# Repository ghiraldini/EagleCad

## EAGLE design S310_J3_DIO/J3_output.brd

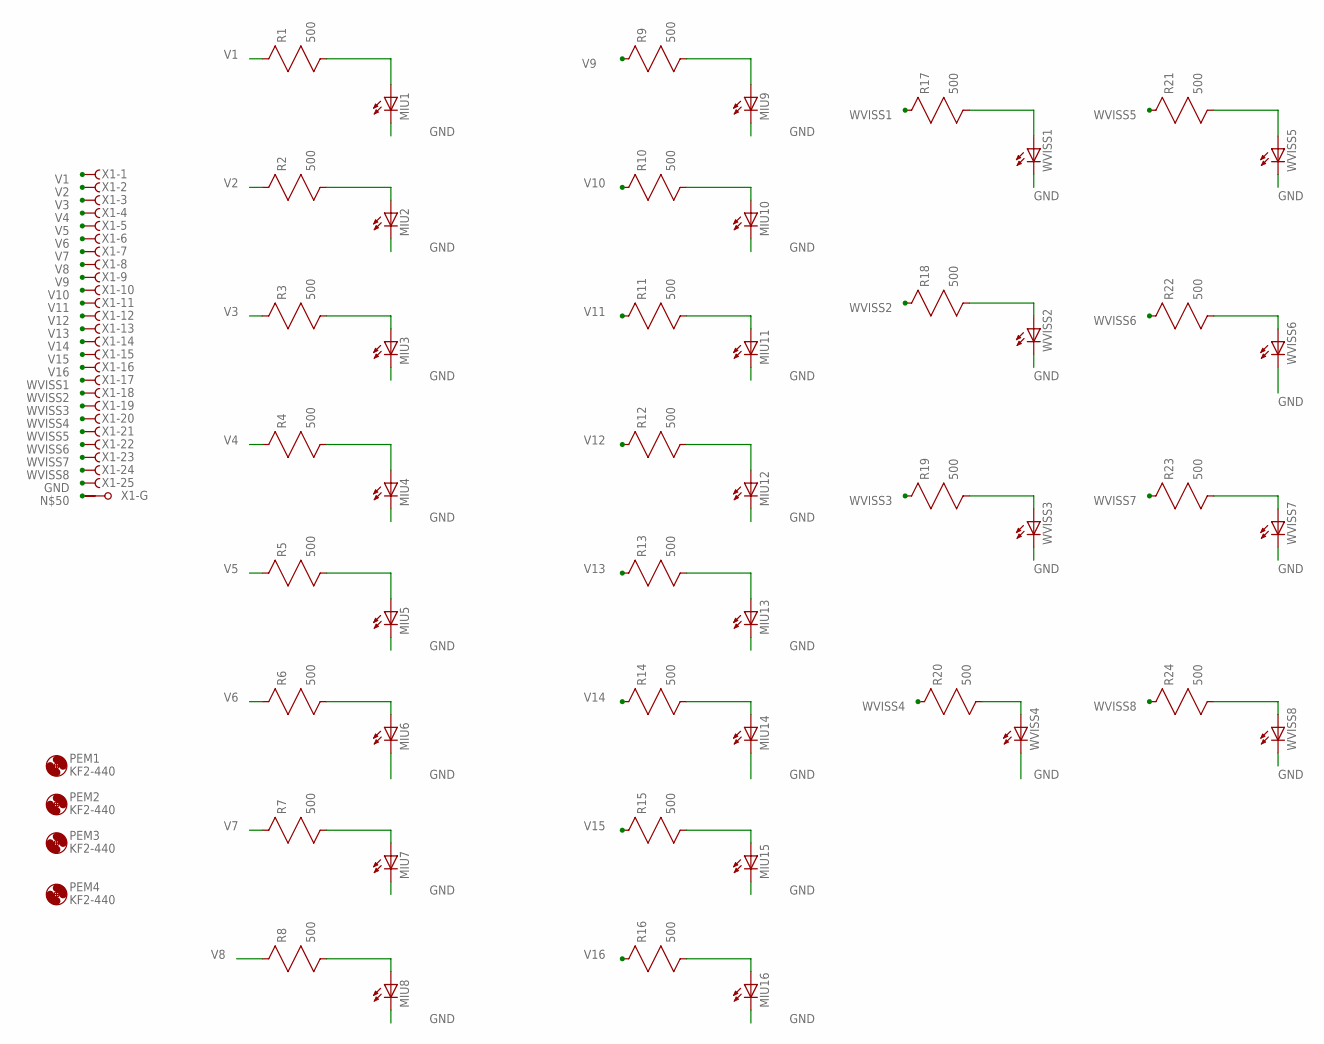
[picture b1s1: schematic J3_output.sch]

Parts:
MIU1, MIU2, MIU3, MIU4, MIU5, MIU6, MIU7, MIU8, MIU9, MIU10, MIU11, MIU12, MIU13, MIU14, MIU15, MIU16: LED5MM
PEM1, PEM2, PEM3, PEM4: KF2-440
R1, R2, R3, R4, R5, R6, R7, R8, R9, R10, R11, R12, R13, R14, R15, R16, R17, R18, R19, R20, R21, R22, R23, R24: 500; R0805; MPN SFR2500001401FR500
WVISS1, WVISS2, WVISS3, WVISS4, WVISS5, WVISS6, WVISS7, WVISS8: LED5MM
X1: F25HPS; F25HP

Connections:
GND: MIU1.K (C), MIU2.K (C), MIU3.K (C), MIU4.K (C), MIU5.K (C), MIU6.K (C), MIU7.K (C), MIU8.K (C), MIU9.K (C), MIU10.K (C), MIU11.K (C), MIU12.K (C), MIU13.K (C), MIU14.K (C), MIU15.K (C), MIU16.K (C), WVISS1.K (C), WVISS2.K (C), WVISS3.K (C), WVISS4.K (C), WVISS5.K (C), WVISS6.K (C), WVISS7.K (C), WVISS8.K (C), X1.25 (F)
unnamed: MIU1.A, R1.2 (B)
unnamed: MIU2.A, R2.2 (B)
unnamed: MIU3.A, R3.2 (B)
unnamed: MIU4.A, R4.2 (B)
unnamed: MIU5.A, R5.2 (B)
unnamed: MIU6.A, R6.2 (B)
unnamed: MIU7.A, R7.2 (B)
unnamed: MIU8.A, R8.2 (B)
unnamed: MIU9.A, R9.2 (B)
unnamed: MIU10.A, R10.2 (B)
unnamed: MIU11.A, R11.2 (B)
unnamed: MIU12.A, R12.2 (B)
unnamed: MIU13.A, R13.2 (B)
unnamed: MIU14.A, R14.2 (B)
unnamed: MIU15.A, R15.2 (B)
unnamed: MIU16.A, R16.2 (B)
unnamed: R17.2 (B), WVISS1.A
unnamed: R18.2 (B), WVISS2.A
unnamed: R19.2 (B), WVISS3.A
unnamed: R20.2 (B), WVISS4.A
unnamed: R21.2 (B), WVISS5.A
unnamed: R22.2 (B), WVISS6.A
unnamed: R23.2 (B), WVISS7.A
unnamed: R24.2 (B), WVISS8.A
V1: R1.1 (A), X1.1 (F)
V2: R2.1 (A), X1.2 (F)
V3: R3.1 (A), X1.3 (F)
V4: R4.1 (A), X1.4 (F)
V5: R5.1 (A), X1.5 (F)
V6: R6.1 (A), X1.6 (F)
V7: R7.1 (A), X1.7 (F)
V8: R8.1 (A), X1.8 (F)
V9: R9.1 (A), X1.9 (F)
V10: R10.1 (A), X1.10 (F)
V11: R11.1 (A), X1.11 (F)
V12: R12.1 (A), X1.12 (F)
V13: R13.1 (A), X1.13 (F)
V14: R14.1 (A), X1.14 (F)
V15: R15.1 (A), X1.15 (F)
V16: R16.1 (A), X1.16 (F)
WVISS1: R17.1 (A), X1.17 (F)
WVISS2: R18.1 (A), X1.18 (F)
WVISS3: R19.1 (A), X1.19 (F)
WVISS4: R20.1 (A), X1.20 (F)
WVISS5: R21.1 (A), X1.21 (F)
WVISS6: R22.1 (A), X1.22 (F)
WVISS7: R23.1 (A), X1.23 (F)
WVISS8: R24.1 (A), X1.24 (F)

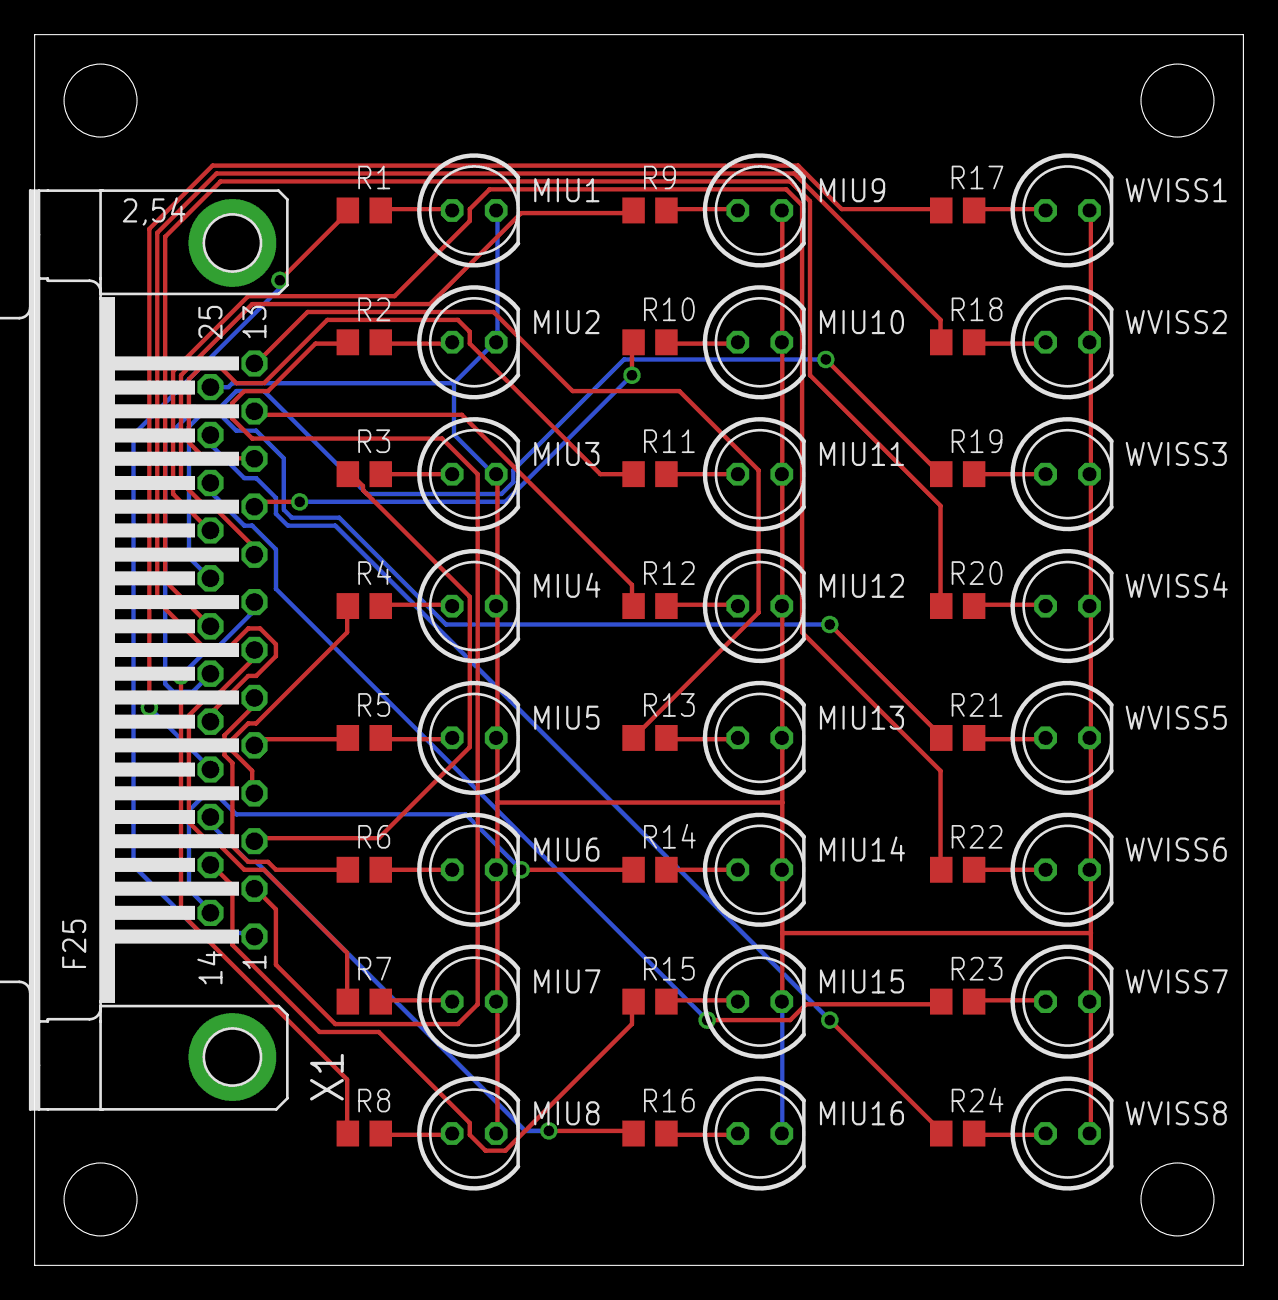
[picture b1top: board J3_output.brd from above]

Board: 2 copper layers, 69.8 x 71.1 mm, 53 parts (0 on the bottom side), 49 nets.

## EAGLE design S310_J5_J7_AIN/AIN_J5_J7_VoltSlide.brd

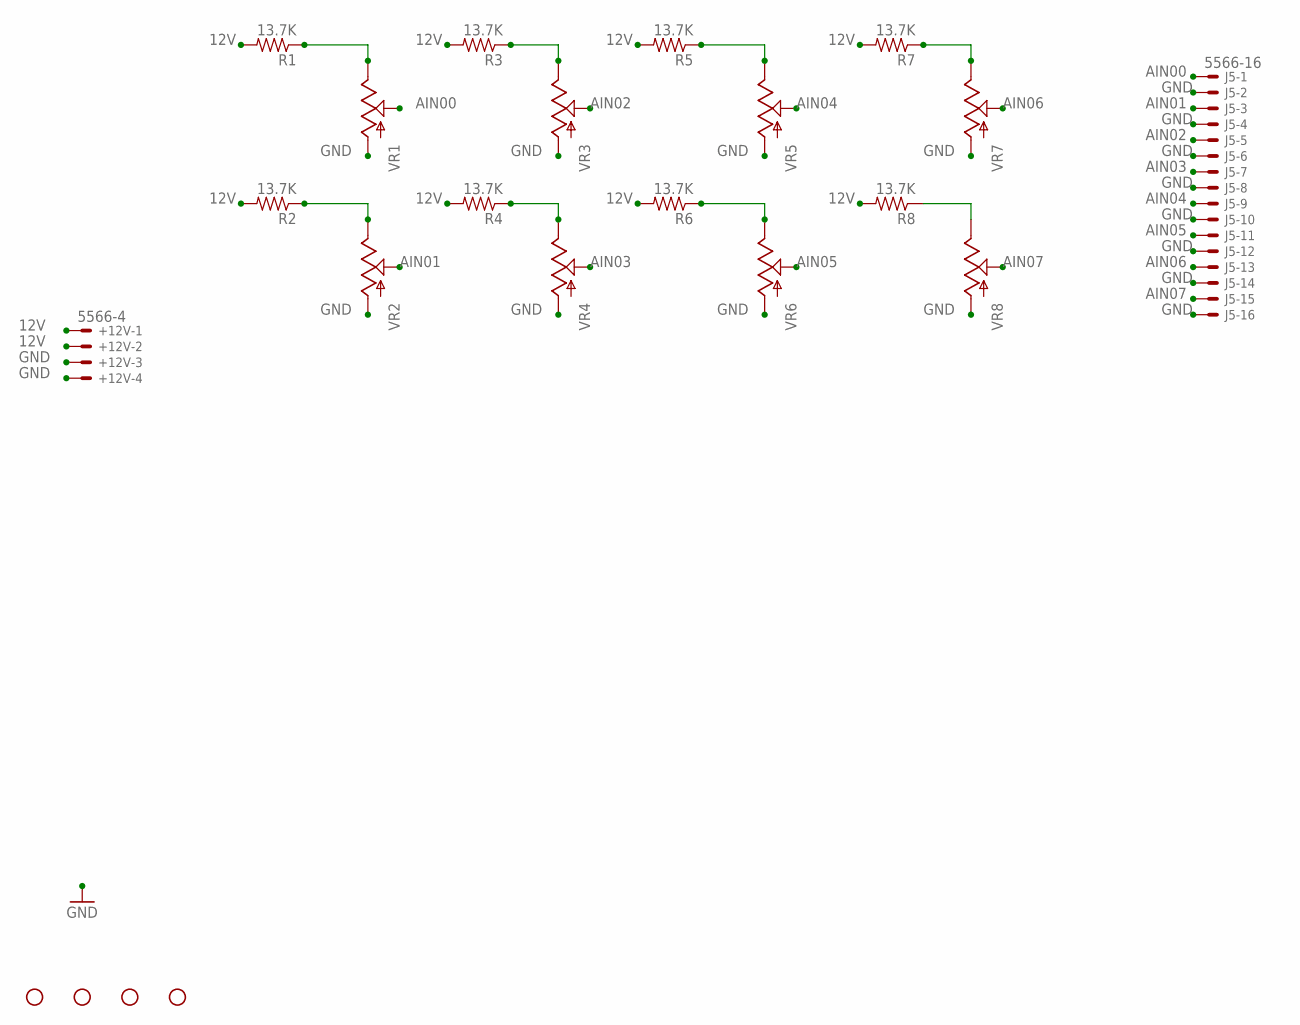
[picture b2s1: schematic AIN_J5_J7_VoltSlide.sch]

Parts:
+12V: 5566-4
H1, H2, H3, H4: STAND-OFF
J5: 5566-16
R1, R2, R3, R4, R5, R6, R7, R8: 13.7K; 0603-RES
VR1, VR2, VR3, VR4, VR5, VR6, VR7, VR8: SLIDER30MM; SLIDER-MEDIUM

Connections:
12V: +12V.1, +12V.2, R1.2, R2.2, R3.2, R4.2, R5.2, R6.2, R7.2, R8.2
AIN00: J5.1, VR1.WIPER (S)
AIN01: J5.3, VR2.WIPER (S)
AIN02: J5.5, VR3.WIPER (S)
AIN03: J5.7, VR4.WIPER (S)
AIN04: J5.9, VR5.WIPER (S)
AIN05: J5.11, VR6.WIPER (S)
AIN06: J5.13, VR7.WIPER (S)
AIN07: J5.15, VR8.WIPER (S)
GND: +12V.3, +12V.4, J5.2, J5.4, J5.6, J5.8, J5.10, J5.12, J5.14, J5.16, VR1.BOTTOM (A), VR2.BOTTOM (A), VR3.BOTTOM (A), VR4.BOTTOM (A), VR5.BOTTOM (A), VR6.BOTTOM (A), VR7.BOTTOM (A), VR8.BOTTOM (A)
unnamed: R8.1, VR8.TOP (E)
unnamed: R1.1, VR1.TOP (E)
unnamed: R3.1, VR3.TOP (E)
unnamed: R5.1, VR5.TOP (E)
unnamed: R6.1, VR6.TOP (E)
unnamed: R2.1, VR2.TOP (E)
unnamed: R4.1, VR4.TOP (E)
unnamed: R7.1, VR7.TOP (E)

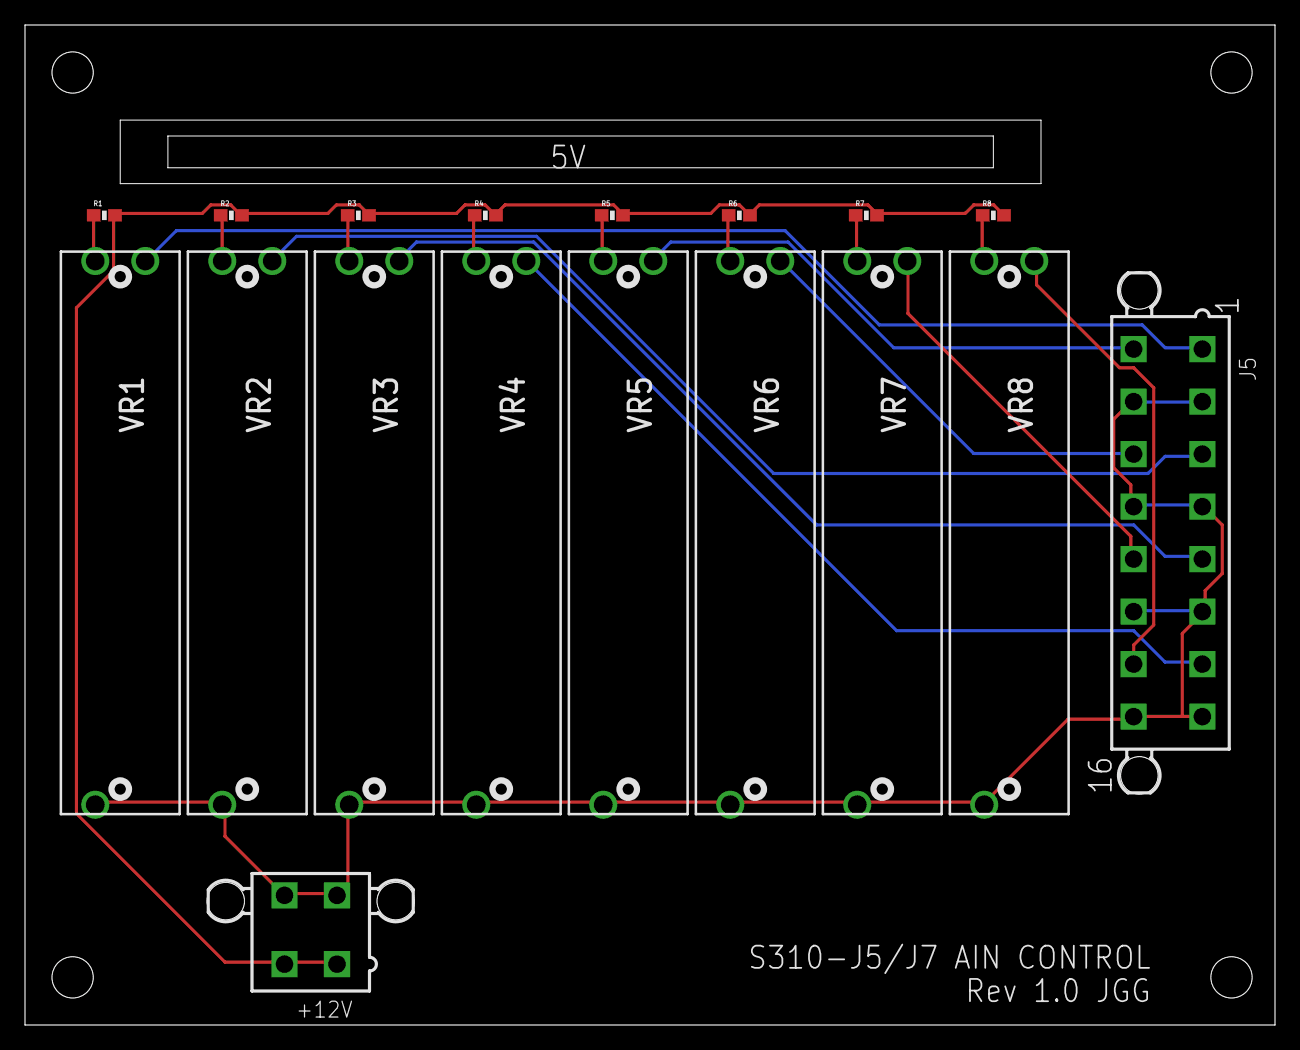
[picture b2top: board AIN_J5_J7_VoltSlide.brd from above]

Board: 2 copper layers, 100.0 x 80.0 mm, 22 parts (0 on the bottom side), 18 nets.

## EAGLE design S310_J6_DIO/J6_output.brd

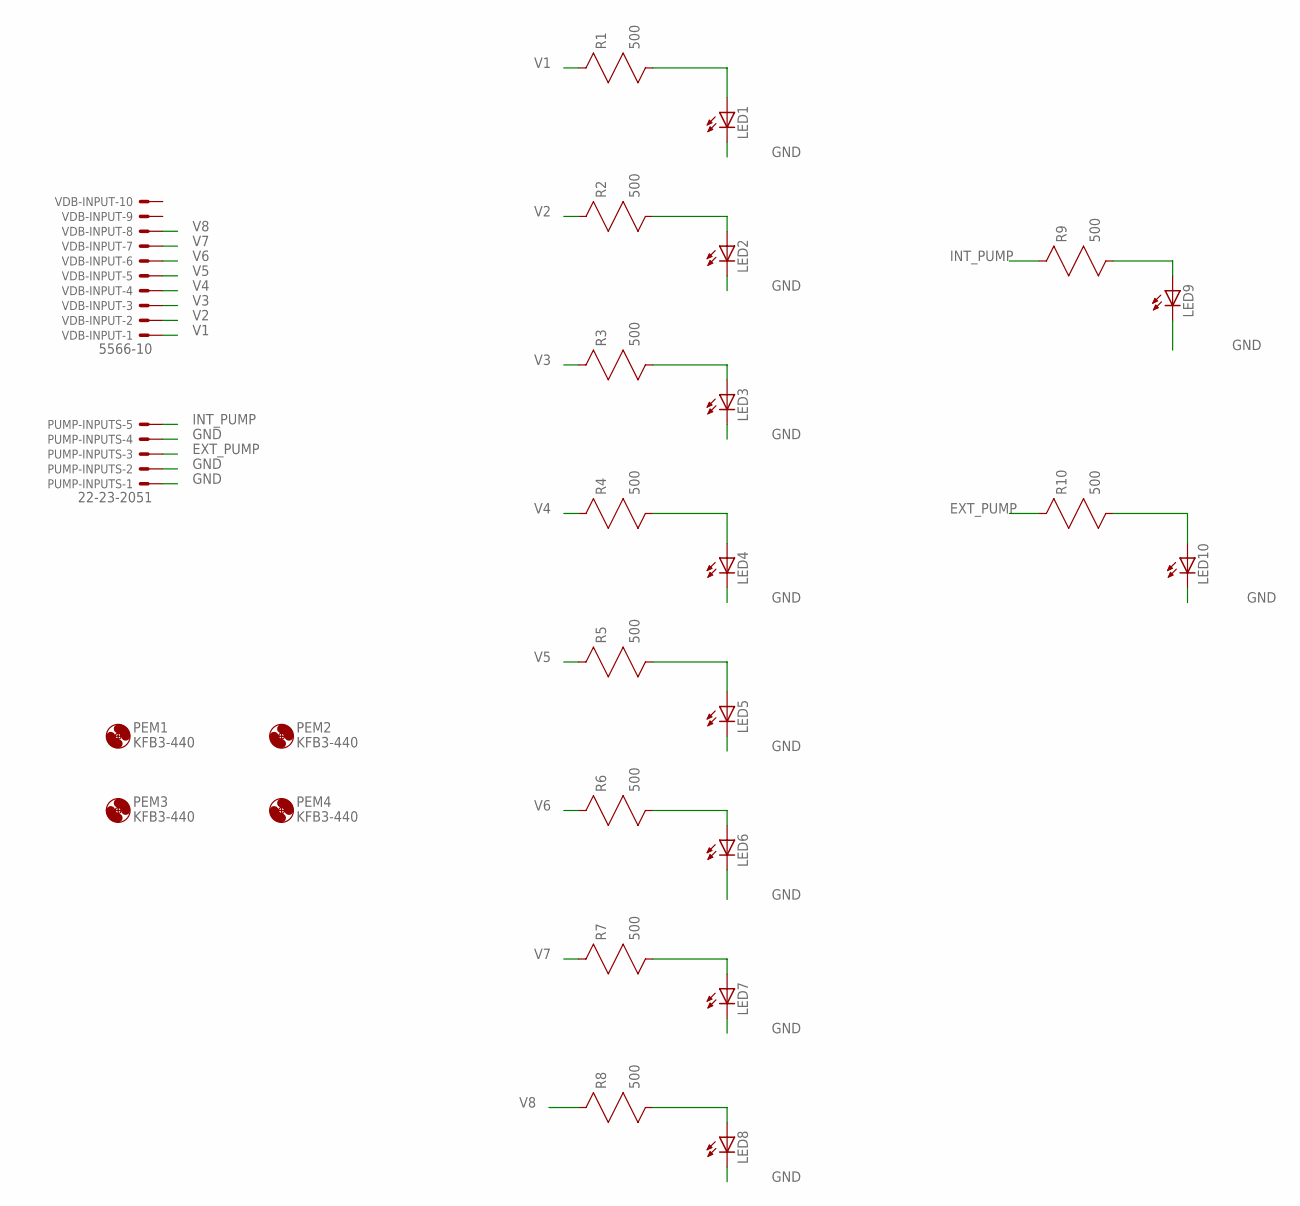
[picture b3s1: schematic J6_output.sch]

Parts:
LED1, LED2, LED3, LED4, LED5, LED6, LED7, LED8, LED9, LED10: LED10MM
PEM1, PEM2, PEM3, PEM4: KFB3-440
PUMP-INPUTS: 22-23-2051
R1, R2, R3, R4, R5, R6, R7, R8, R9, R10: 500; R0805; MPN SFR2500001401FR500
VDB-INPUT: 5566-10; MPN 39-29-6108

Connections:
EXT_PUMP: PUMP-INPUTS.3, R10.1 (A)
GND: LED1.K (C), LED2.K (C), LED3.K (C), LED4.K (C), LED5.K (C), LED6.K (C), LED7.K (C), LED8.K (C), LED9.K (C), LED10.K (C), PUMP-INPUTS.1, PUMP-INPUTS.2, PUMP-INPUTS.4
INT_PUMP: PUMP-INPUTS.5, R9.1 (A)
unnamed: LED1.A, R1.2 (B)
unnamed: LED2.A, R2.2 (B)
unnamed: LED3.A, R3.2 (B)
unnamed: LED4.A, R4.2 (B)
unnamed: LED5.A, R5.2 (B)
unnamed: LED6.A, R6.2 (B)
unnamed: LED7.A, R7.2 (B)
unnamed: LED8.A, R8.2 (B)
unnamed: LED9.A, R9.2 (B)
unnamed: LED10.A, R10.2 (B)
V1: R1.1 (A), VDB-INPUT.1
V2: R2.1 (A), VDB-INPUT.2
V3: R3.1 (A), VDB-INPUT.3
V4: R4.1 (A), VDB-INPUT.4
V5: R5.1 (A), VDB-INPUT.5
V6: R6.1 (A), VDB-INPUT.6
V7: R7.1 (A), VDB-INPUT.7
V8: R8.1 (A), VDB-INPUT.8

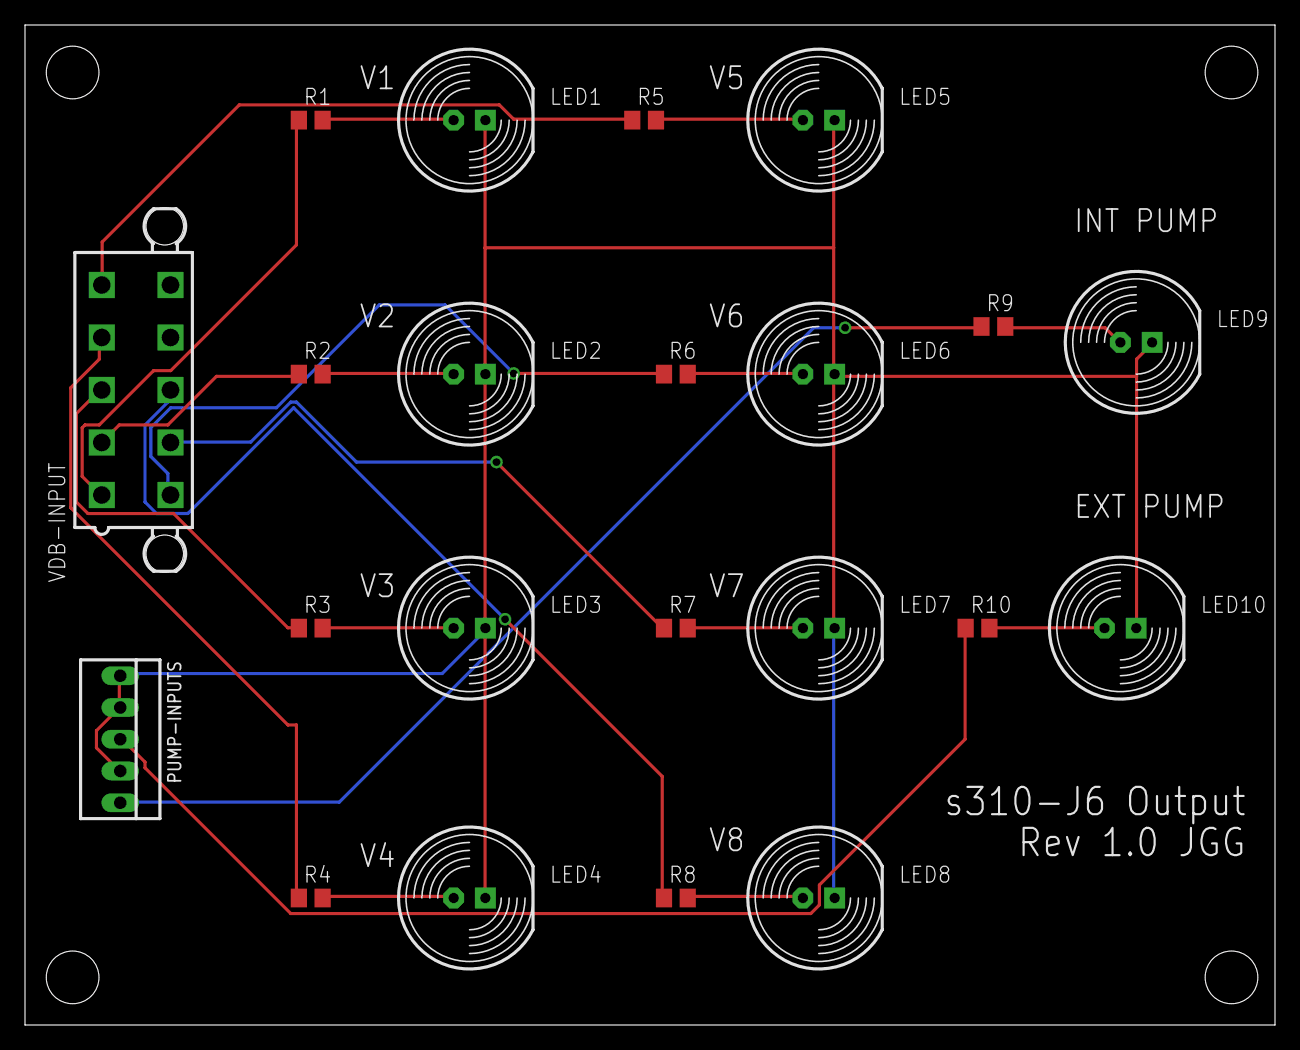
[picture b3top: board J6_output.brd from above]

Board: 2 copper layers, 100.0 x 80.0 mm, 26 parts (0 on the bottom side), 21 nets.

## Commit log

2016-11-18 Initial Upload
    Simple control & status boards for LGR

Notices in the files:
parts and their libraries:
penn-engineering: Copyright (C) 2010, Bob Starr
SparkFun-Electromechanical: Licensing: Creative Commons ShareAlike 4.0 International - https://creativecommons.org/licenses/by-sa/4.0
